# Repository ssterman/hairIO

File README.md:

# HairIO

Human hair is a cultural material, with a rich history displaying individuality, cultural expression and group identity.  It is malleable in length,  color and style,  highly visible,  and embedded in a range of personal and group interactions. As wearable technologies move ever closer to the body, and embodied interactions become more common and desirable, hair presents a unique and little-explored site for novel interactions. In this paper, we present an exploration and working prototype of hair as a site for novel interaction, leveraging its position as something both public and private,  social and personal, malleable and permanent. We develop applications and interactions around this new material in HäirIÖ: a novel integration of hair-based technologies and braids that combine capacitive touch input and dynamic output through color and shape change. Finally, we evaluate this hair-based interactive technology with users, including the integration of HäirIÖ within the landscape of existing wearable and mobile technologies.

Work by: Christine Dierk, Sarah Sterman, Molly Jane Nicholas, Eric Paulos

Hybrid Ecologies Lab
hybrid-ecologies.org

[Video](https://www.youtube.com/watch?v=8JV2D7gJ5HI)

[Paper](https://dl.acm.org/citation.cfm?id=3173232)

## Arduino sketches

In this repo you will find example sketches for use on the HairIO PCB, demonstrating capacitive touch, actuation, and bluetooth control.  

*demo_captouch:* A basic sketch showing only capacitive touch sensing with manually defined sensing thresholds. The onboard LED will light when a touch is identified.

*demo_timing*: A basic sketch showing only actuation.  Every period of x seconds, the braid will actuate, then turn off.  The onboard LED will light when the braid is actuating.

*demo_pcb_bluetooth_with_drive_captouch*: All-inclusive demo that uses the Adafruit Bluetooth app to provide touch feedback and control actuation through the bluetooth chip. 

All hardware pins are defined assuming the PCB version of the HairIO circuit, though all pin mappings should be double-checked when you make your own hardware. 

## Eagle Files

In *hairio_full_3* you will find the Eagle schematic and board file for the integrated PCB version of the HairIO circuit. 

## Instructable

For a full description of this project, please see the [Instructable](https://www.instructables.com/id/HairIO-Hair-As-Interactive-Material/)

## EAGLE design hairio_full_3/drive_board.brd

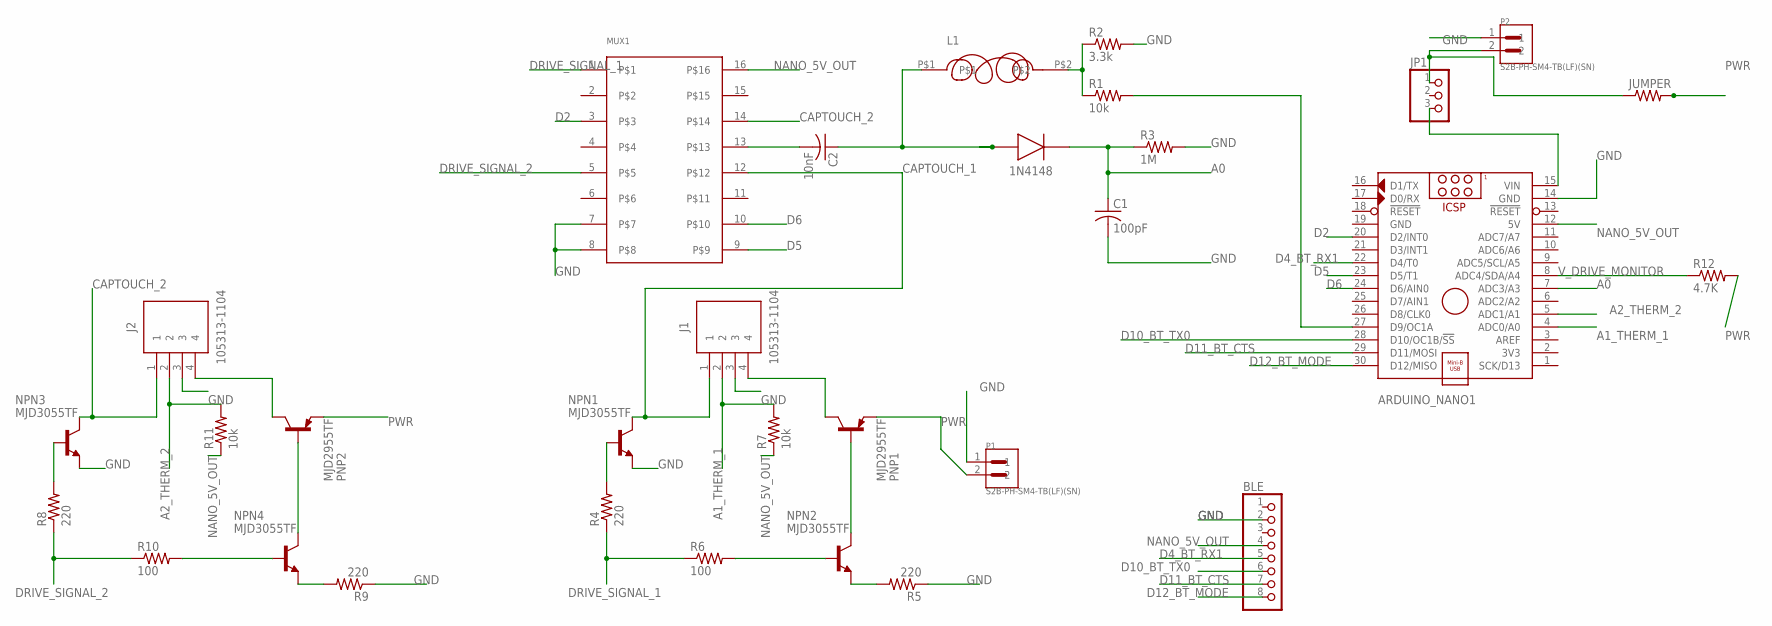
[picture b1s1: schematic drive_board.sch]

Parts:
1N4148: 1N5819HW-7-F; SOD3716X145N
ARDUINO_NANO1: ARDUINO_NANO
BLE: PINHD-1X8; 1X08
C1: 100pF; C0805
C2: 10nF; C0805
J1, J2: 105313-1104
JP1: PINHD-1X3; 1X03
JUMPER: R-US_R0805; R0805
L1: SRE6603
MUX1: HAIRIO_MUX; SO16
NPN1, NPN2, NPN3, NPN4: MJD3055TF; DPAK
P1, P2: S2B-PH-SM4-TB(LF)(SN); JST_S2B-PH-SM4-TB(LF)(SN)
PNP1, PNP2: MJD2955TF; DPAK
R1, R7, R11: 10k; R0805
R2: 3.3k; R0805
R3: 1M; R0805
R4, R5, R8, R9: 220; R0805
R6, R10: 100; R0805
R12: 4.7K; R0805

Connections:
A0: 1N4148.1 (K), ARDUINO_NANO1.7 (ADC3/A3), C1.1, R3.1
A1_THERM_1: ARDUINO_NANO1.4 (ADC0/A0), J1.2, R7.2
A2_THERM_2: ARDUINO_NANO1.5 (ADC1/A1), J2.2, R11.2
CAPTOUCH_1: J1.1, MUX1.12, NPN1.4 (C)
CAPTOUCH_2: J2.1, MUX1.14, NPN3.4 (C)
D2: ARDUINO_NANO1.20 (D2/INT0), MUX1.3
D4_BT_RX1: ARDUINO_NANO1.22 (D4/T0), BLE.5
D5: ARDUINO_NANO1.23 (D5/T1), MUX1.9
D6: ARDUINO_NANO1.24 (D6/AIN0), MUX1.10
D10_BT_TX0: ARDUINO_NANO1.28 (D10/OC1B/!SS), BLE.6
D11_BT_CTS: ARDUINO_NANO1.29 (D11/MOSI), BLE.7
D12_BT_MODE: ARDUINO_NANO1.30 (D12/MISO), BLE.8
DRIVE_SIGNAL_1: MUX1.1, R4.1, R6.1
DRIVE_SIGNAL_2: MUX1.5, R8.1, R10.1
GND: ARDUINO_NANO1.14 (GND), ARDUINO_NANO1.19 (GND), BLE.2, C1.2, J1.3, J2.3, MUX1.7, MUX1.8, NPN1.3 (E), NPN3.3 (E), P1.1, P2.1, R2.2, R3.2, R5.1, R9.1
unnamed: NPN2.1 (B), R6.2
unnamed: NPN2.3 (E), R5.2
unnamed: NPN4.1 (B), R10.2
unnamed: NPN2.4 (C), PNP1.1 (B)
unnamed: NPN1.1 (B), R4.2
unnamed: C2.2, MUX1.13
unnamed: 1N4148.2 (A), C2.1, L1.P$1
unnamed: J1.4, PNP1.4 (C)
unnamed: ARDUINO_NANO1.27 (D9/OC1A), R1.2
unnamed: L1.P$2, R1.1, R2.1
unnamed: NPN4.3 (E), R9.2
unnamed: ARDUINO_NANO1.15 (VIN), JP1.3
unnamed: NPN4.4 (C), PNP2.1 (B)
unnamed: NPN3.1 (B), R8.2
unnamed: J2.4, PNP2.4 (C)
unnamed: JP1.1, JUMPER.1, P2.2
NANO_5V_OUT: ARDUINO_NANO1.12 (5V), BLE.4, MUX1.16, R7.1, R11.1
PWR: JUMPER.2, P1.2, PNP1.3 (E), PNP2.3 (E), R12.2
V_DRIVE_MONITOR: ARDUINO_NANO1.8 (ADC4/SDA/A4), R12.1

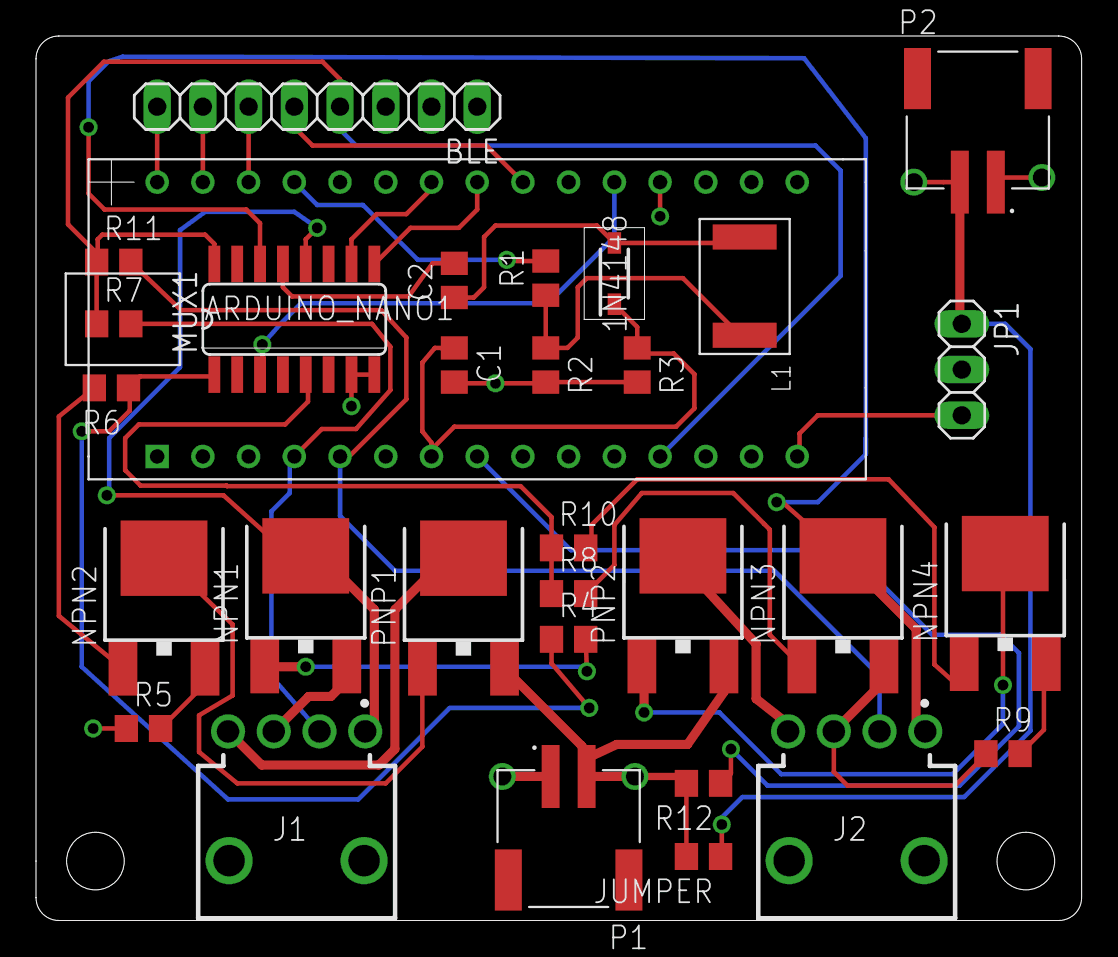
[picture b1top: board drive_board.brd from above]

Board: 2 copper layers, 58.1 x 49.1 mm, 31 parts (0 on the bottom side), 34 nets.

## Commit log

2018-02-27 Initializing the public facing HairIO repository
2018-03-18 initial demo code and eagle files
2018-03-18 readme
2018-03-19 added instructable and paper link
2018-03-19 link formatting?
2018-03-21 updated with captouch
